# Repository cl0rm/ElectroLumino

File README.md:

# ElectroLumino
Portable Mulit-Channel programmable EL wire driver featuring PWM

# Warning
EL Wire is driven with rather high voltages. Only play with high voltages if you know what you're doing!

# Idea
This will become a fancy EL wire driver to make shiny clothing.
It should fit into a pocket (so it will be more or less the size of a typical smart phone)

# Features

- Battery Powered (18650 Cell)
- USB rechargable
- Up to four different EL wire channels
- PWM dimming
- Audio Reactive

- Additional WSxxx Digital LED channel

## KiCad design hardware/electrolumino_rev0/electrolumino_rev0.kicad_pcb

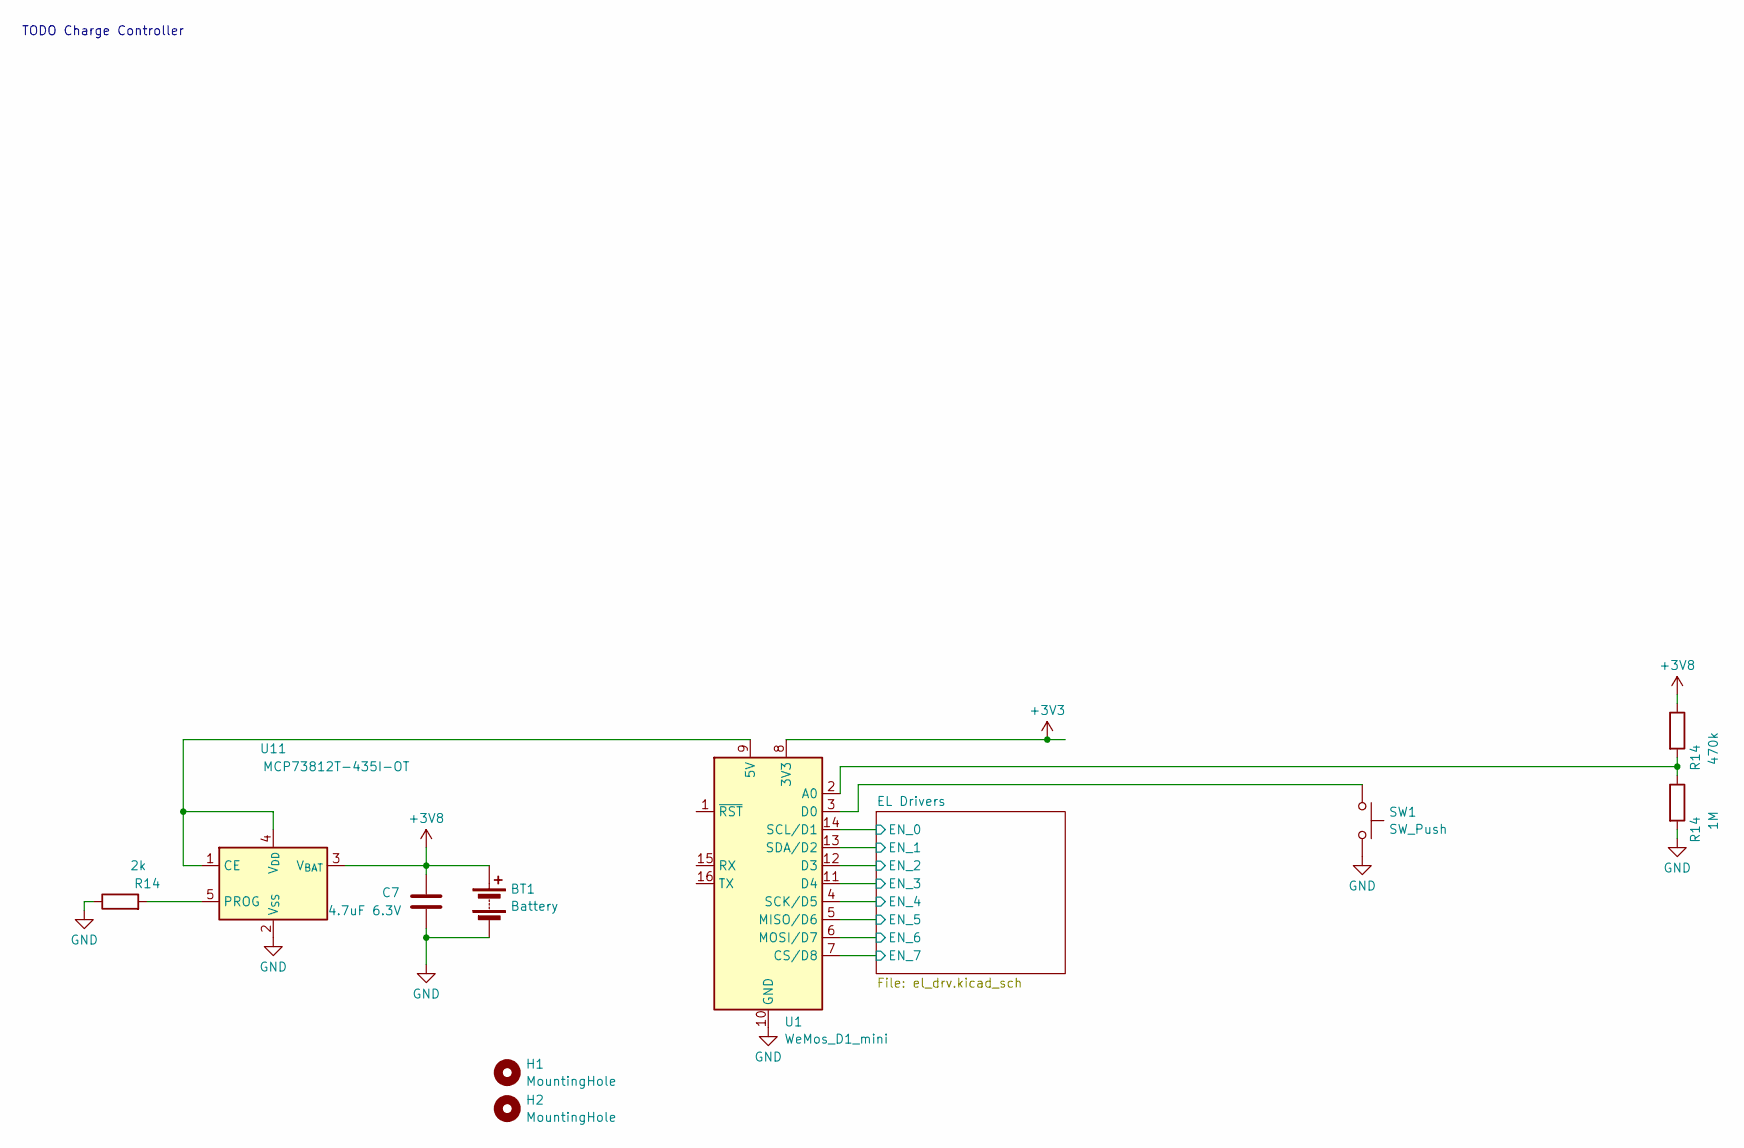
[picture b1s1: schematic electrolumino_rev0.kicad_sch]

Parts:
BT1: Battery; BatteryHolder_MPD_BH-18650-PC2
C7: 4.7uF 6.3V; C_0603_1608Metric
H1, H2: MountingHole; MountingHole_3.2mm_M3
R14: 1M; R_0603_1608Metric
SW1: SW_Push; SW_Tactile_SPST_Angled_PTS645Vx31-2LFS
U1: WeMos_D1_mini; WEMOS_D1_mini_light
U11: MCP73812T-435I-OT; SOT-23-5

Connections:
+3V3: U1.8 (3V3); also elsewhere on the board
/EL Drivers/EN_0: U1.14 (SCL/D1); also elsewhere on the board
/EL Drivers/EN_1: U1.13 (SDA/D2); also elsewhere on the board
/EL Drivers/EN_3: U1.11 (D4); also elsewhere on the board
/EL Drivers/EN_4: U1.4 (SCK/D5); also elsewhere on the board
/EL Drivers/EN_5: U1.5 (MISO/D6); also elsewhere on the board
/EL Drivers/EN_6: U1.6 (MOSI/D7); also elsewhere on the board
/EL Drivers/EN_7: U1.7 (CS/D8); also elsewhere on the board
unnamed: U1.9 (5V), U11.1 (CE), U11.4 (V_{DD})
unnamed: SW1.1, U1.3 (D0)

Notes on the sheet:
TODO Charge Controller

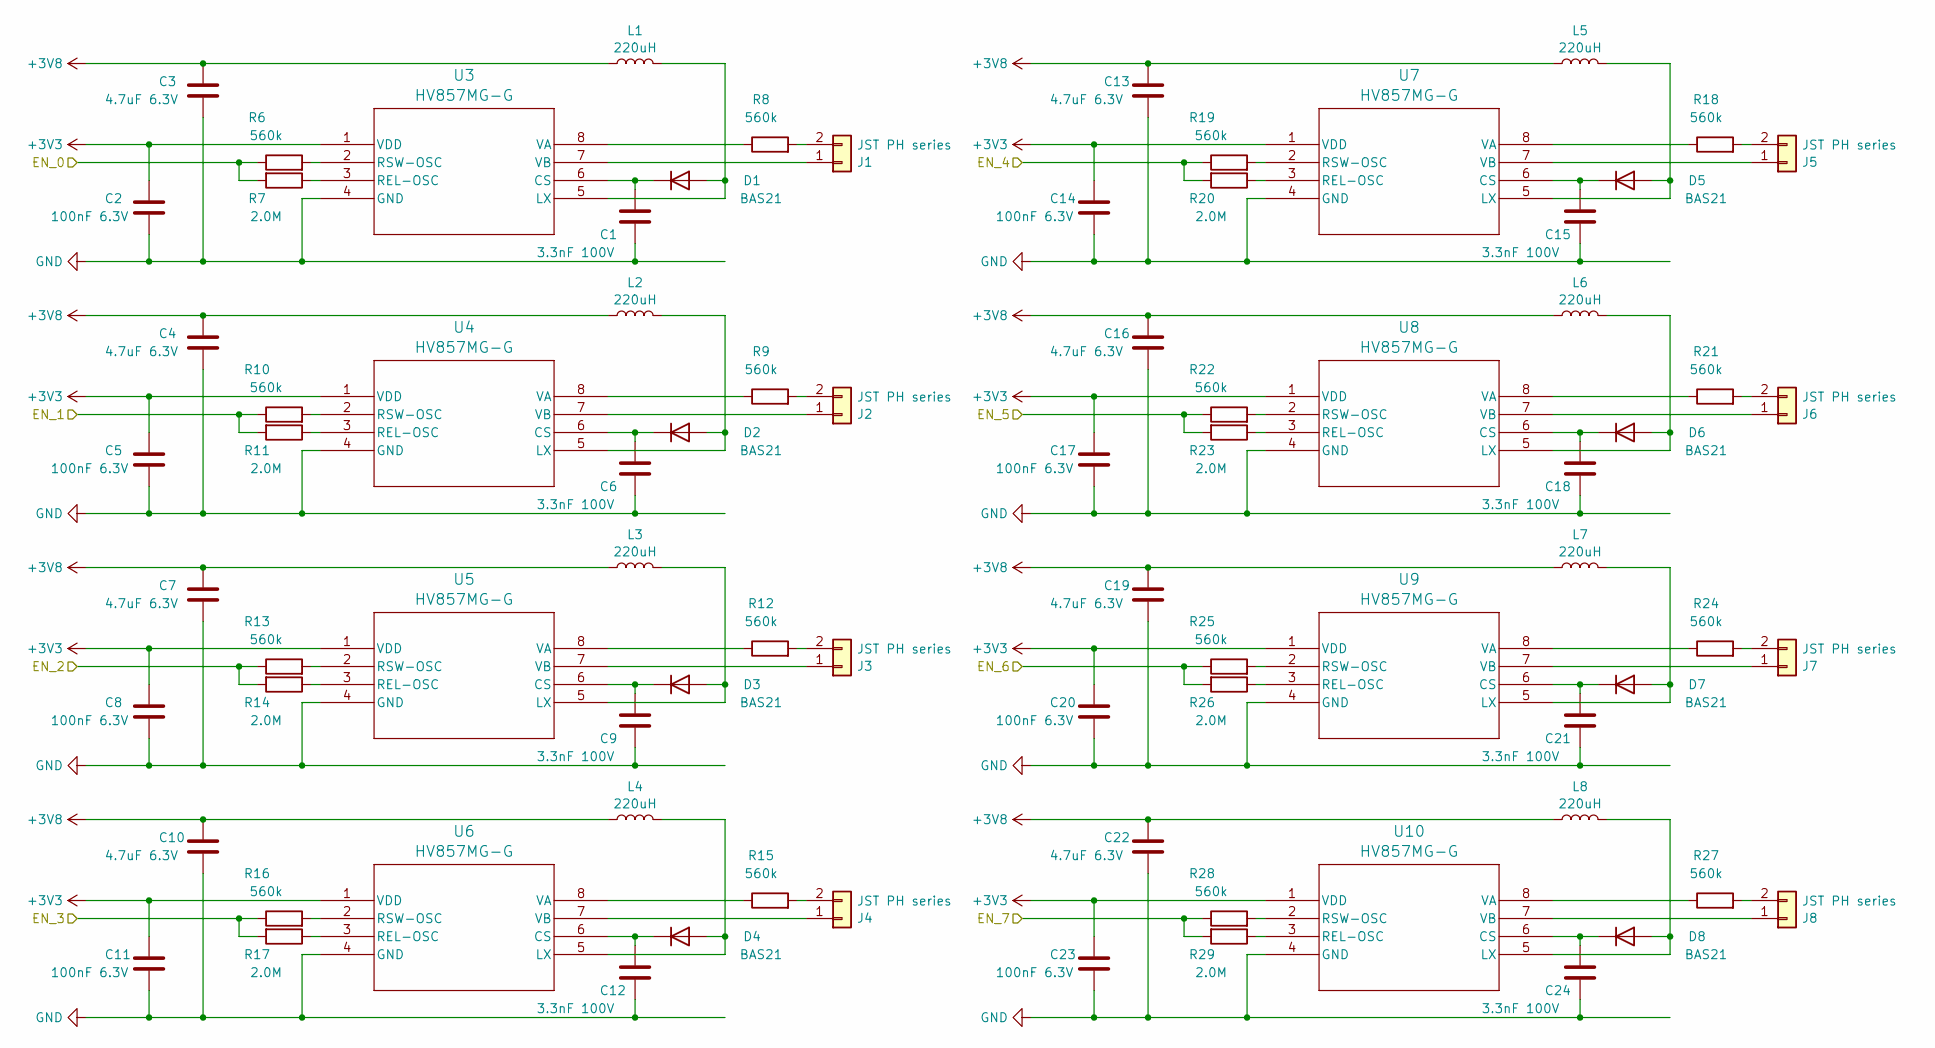
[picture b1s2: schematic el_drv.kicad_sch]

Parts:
C1, C6, C9, C12, C15, C18, C21, C24: 3.3nF 100V; C_0603_1608Metric
C2, C5, C8, C11, C14, C17, C20, C23: 100nF 6.3V; C_0603_1608Metric
C3, C4, C7, C10, C13, C16, C19, C22: 4.7uF 6.3V; C_0603_1608Metric
D1, D2, D3, D4, D5, D6, D7, D8: BAS21; SOT-23
J1, J2, J3, J4, J5, J6, J7, J8: JST PH series; JST_PH_S2B-PH-SM4-TB_1x02-1MP_P2.00mm_Horizontal
L1, L2, L3, L4, L5, L6, L7, L8: 220uH; L_Changjiang_FNR3015S
R6, R10, R13, R16, R19, R22, R25, R28: 560k; R_0603_1608Metric
R7, R11, R14, R17, R20, R23, R26, R29: 2.0M; R_0603_1608Metric
R8, R9, R12, R15, R18, R21, R24, R27: 560k; R_1206_3216Metric
U3, U4, U5, U6, U7, U8, U9, U10: HV857MG-G; MSOP-8_3x3mm_P0.65mm

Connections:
+3V3: C2.1, C5.1, C8.1, C11.1, C14.1, C17.1, C20.1, C23.1, U3.1 (VDD), U4.1 (VDD), U5.1 (VDD), U6.1 (VDD), U7.1 (VDD), U8.1 (VDD), U9.1 (VDD), U10.1 (VDD); also elsewhere on the board
/EL Drivers/EN_0: R6.1, R7.2; also elsewhere on the board
/EL Drivers/EN_1: R10.1, R11.2; also elsewhere on the board
/EL Drivers/EN_3: R16.1, R17.2; also elsewhere on the board
/EL Drivers/EN_4: R19.1, R20.2; also elsewhere on the board
/EL Drivers/EN_5: R22.1, R23.2; also elsewhere on the board
/EL Drivers/EN_6: R25.1, R26.2; also elsewhere on the board
/EL Drivers/EN_7: R28.1, R29.2; also elsewhere on the board
unnamed: D1.1 (A), L1.2, U3.5 (LX)
unnamed: C1.1, D1.3 (K), U3.6 (CS)
unnamed: D2.1 (A), L2.2, U4.5 (LX)
unnamed: C6.1, D2.3 (K), U4.6 (CS)
unnamed: D3.1 (A), L3.2, U5.5 (LX)
unnamed: C9.1, D3.3 (K), U5.6 (CS)
unnamed: D4.1 (A), L4.2, U6.5 (LX)
unnamed: C12.1, D4.3 (K), U6.6 (CS)
unnamed: D5.1 (A), L5.2, U7.5 (LX)
unnamed: C15.1, D5.3 (K), U7.6 (CS)
unnamed: D6.1 (A), L6.2, U8.5 (LX)
unnamed: C18.1, D6.3 (K), U8.6 (CS)
unnamed: D7.1 (A), L7.2, U9.5 (LX)
unnamed: C21.1, D7.3 (K), U9.6 (CS)
unnamed: D8.1 (A), L8.2, U10.5 (LX)
unnamed: C24.1, D8.3 (K), U10.6 (CS)
unnamed: J1.1, U3.7 (VB)
unnamed: J1.2, R8.2
unnamed: J2.1, U4.7 (VB)
unnamed: J2.2, R9.2
unnamed: J3.1, U5.7 (VB)
unnamed: J3.2, R12.2
unnamed: J4.1, U6.7 (VB)
unnamed: J4.2, R15.2
unnamed: J5.1, U7.7 (VB)
unnamed: J5.2, R18.2
unnamed: J6.1, U8.7 (VB)
unnamed: J6.2, R21.2
unnamed: J7.1, U9.7 (VB)
unnamed: J7.2, R24.2
unnamed: J8.1, U10.7 (VB)
unnamed: J8.2, R27.2
unnamed: R7.1, U3.3 (REL-OSC)
unnamed: R6.2, U3.2 (RSW-OSC)
unnamed: R8.1, U3.8 (VA)
unnamed: R11.1, U4.3 (REL-OSC)
unnamed: R10.2, U4.2 (RSW-OSC)
unnamed: R9.1, U4.8 (VA)
unnamed: R13.2, U5.2 (RSW-OSC)
unnamed: R12.1, U5.8 (VA)
unnamed: R17.1, U6.3 (REL-OSC)
unnamed: R16.2, U6.2 (RSW-OSC)
unnamed: R15.1, U6.8 (VA)
unnamed: R20.1, U7.3 (REL-OSC)
unnamed: R19.2, U7.2 (RSW-OSC)
unnamed: R18.1, U7.8 (VA)
unnamed: R23.1, U8.3 (REL-OSC)
unnamed: R22.2, U8.2 (RSW-OSC)
unnamed: R21.1, U8.8 (VA)
unnamed: R26.1, U9.3 (REL-OSC)
unnamed: R25.2, U9.2 (RSW-OSC)
unnamed: R24.1, U9.8 (VA)
unnamed: R29.1, U10.3 (REL-OSC)
unnamed: R28.2, U10.2 (RSW-OSC)
unnamed: R27.1, U10.8 (VA)

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
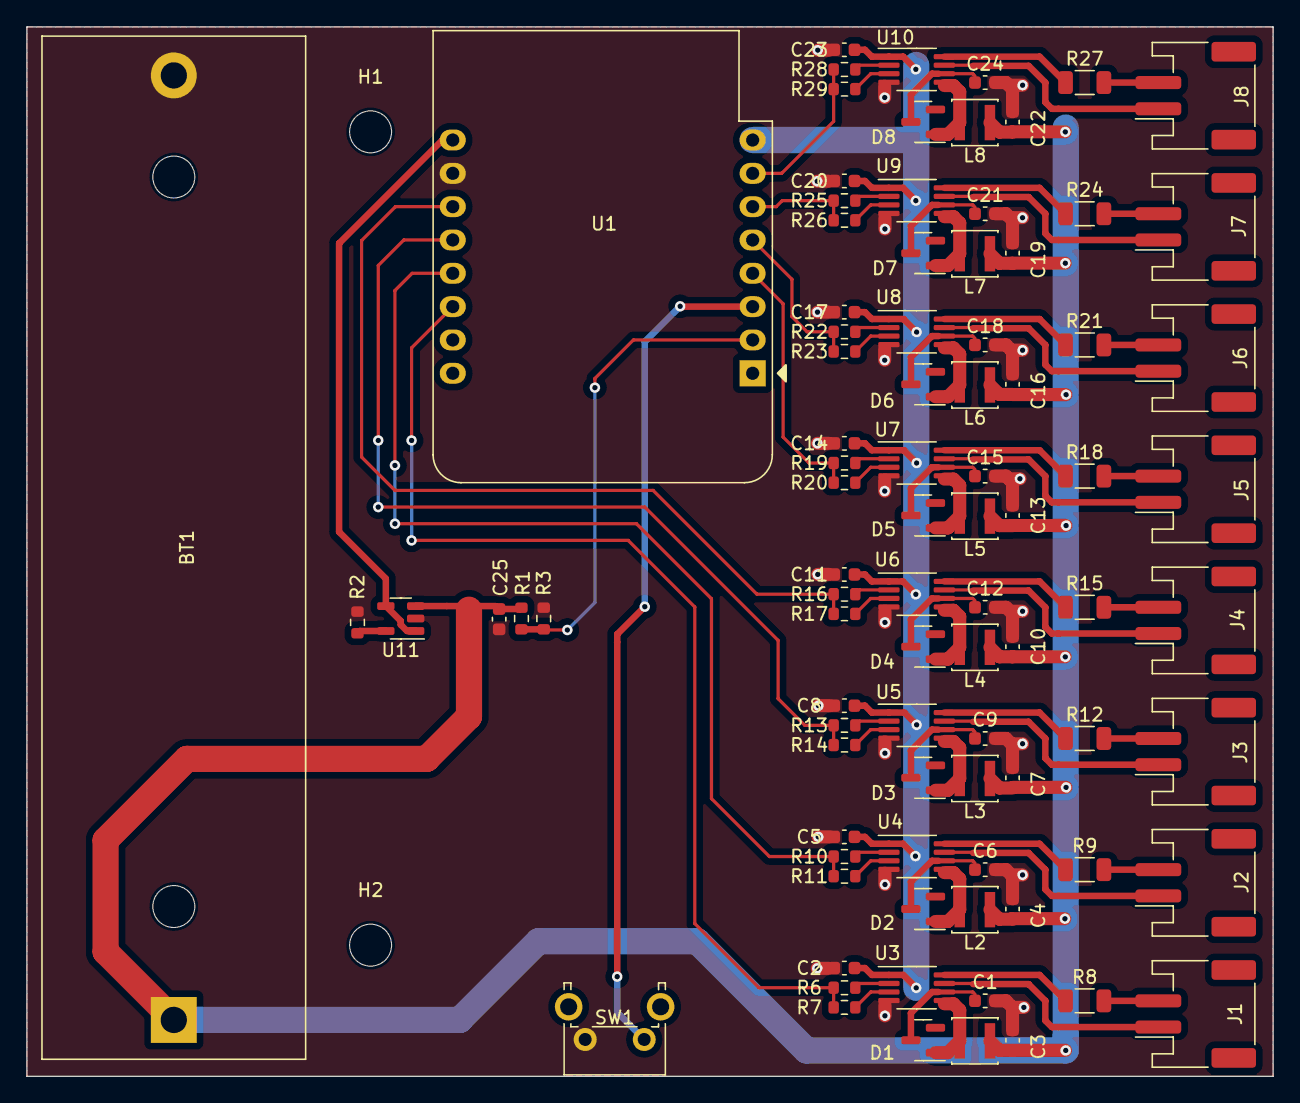
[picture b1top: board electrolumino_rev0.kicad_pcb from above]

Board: 2 copper layers, 95.0 x 80.0 mm, 90 parts (0 on the bottom side), 71 nets.

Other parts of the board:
C25: 4.7uF 6.3V; C_0603_1608Metric
R1: 470k; R_0603_1608Metric
R2: 2k; R_0603_1608Metric
R3: 1M; R_0603_1608Metric

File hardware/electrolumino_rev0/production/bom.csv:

Designator,Footprint,Quantity,Value,LCSC Part #
BT1,BatteryHolder_MPD_BH-18650-PC2,1,Battery,
"C1, C12, C15, C18, C21, C24, C6, C9",0603,8,3.3nF 100V,
"C10, C13, C16, C19, C22, C25, C3, C4, C7",0603,9,4.7uF 6.3V,
"C11, C14, C17, C2, C20, C23, C5, C8",0603,8,100nF 6.3V,
"D1, D2, D3, D4, D5, D6, D7, D8",SOT-23,8,BAS21,
"H1, H2",MountingHole_3.2mm_M3,2,MountingHole,
"J1, J2, J3, J4, J5, J6, J7, J8",JST_PH_S2B-PH-SM4-TB_1x02-1MP_P2.00mm_Horizontal,8,JST PH series,
"L1, L2, L3, L4, L5, L6, L7, L8",L_Changjiang_FNR3015S,8,220uH,
R1,0603,1,470k,
"R10, R13, R16, R19, R22, R25, R28, R6",0603,8,560k,
"R11, R14, R17, R20, R23, R26, R29, R7",0603,8,2.0M,
"R12, R15, R18, R21, R24, R27, R8, R9",1206,8,560k,
R2,0603,1,2k,
R3,0603,1,1M,
SW1,SW_Tactile_SPST_Angled_PTS645Vx31-2LFS,1,SW_Push,
U1,WEMOS_D1_mini_light,1,WeMos_D1_mini,
"U10, U3, U4, U5, U6, U7, U8, U9",MSOP-8_3x3mm_P0.65mm,8,HV857MG-G,
U11,SOT-23-5,1,MCP73812T-435I-OT,

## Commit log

2024-07-15 hardware rev0
